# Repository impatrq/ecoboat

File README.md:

# EcoBoat
Bienvenidos al repositorio de EcoBoat.

## Software

En la carpeta de "Software" se encontrarán con varios archivos:

- EcoBoat1.0: Es el código principal, donde se ejecuta el funcionamiento del barco y todas las librerías utilizadas para dicho fin.
- Motores: Es la librería (desarrollada por el equipo de EcoBoat) que se utiliza para controlar los motores.
- SensoresUS: Es la librería (desarrollada por el equipo de EcoBoat) que utilizamos para realizar las mediciones con los sensores Ultrasónicos.
- RedNeuronal: Es la librería (desarrollada por el equipo de EcoBoat) que contiene el código de la Red Neuronal y su entrenamiento.
- Módulo_Master: Es el programa utilizado para recibir la información y transferirla mediante sockets a la Interfaz de Usuario.
- Interfaz de Usuario: En esta carpeta se encuentran los códigos de la interfaz de usuario.
- Simulación: En esta carpeta encontrarán todo lo relacionado al entrenamiento de la Red Neuronal.
  - Aplicación Ejecutable: Aquí se encuentra la aplicación de la cual se obtienen los datos de entrenamiento para la red, es decir, la red aprende de las acciones realizadas en dicha aplicación.
  - Código fuente: Contiene el programa de la simulación.
  - trainData: En esta carpeta se guardan los archivos con la información de entrenamiento.

## Hardware

En esta carpeta se encuentran los diseños de todas las placas utilizadas:

- Circuito de Control de Marcha: Circuito utilizado para controlar los 3 motores del EcoBoat
- Fuente de 12V a 5V: regulador de tensión de 12 a 5V.
- Regulador de Carga: Es el circuito que controla la carga de la batería utilizando un panel solar.
- SensoresUS: Esta placa cumple la función de sincronizar la toma de datos de los sensores Ultrasónicos.
- Diagrama de Interconexión de circuitos: Es un diagrama que muestra como se conectan todas las placas del proyecto.

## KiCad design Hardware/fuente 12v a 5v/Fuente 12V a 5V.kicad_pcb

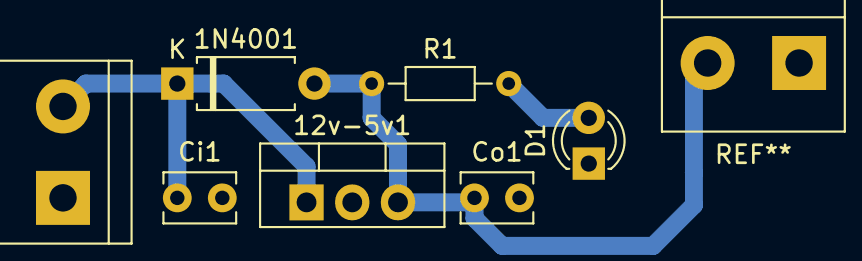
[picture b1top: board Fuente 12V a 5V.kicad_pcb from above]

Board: 2 copper layers, 7 parts (0 on the bottom side), 4 nets.

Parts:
1N4001: D; D_A-405_P7.62mm_Horizontal
12v-5v1: LM7805_TO220; TO-220-3_Vertical
Ci1: 330n; C_Disc_D3.8mm_W2.6mm_P2.50mm
Co1: 100n; C_Disc_D3.8mm_W2.6mm_P2.50mm
D1: LED; LED_D3.0mm
R1: 1K; R_Axial_DIN0204_L3.6mm_D1.6mm_P7.62mm_Horizontal
input-12v1: 12v; TerminalBlock_bornier-2_P5.08mm

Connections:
GND: 12v-5v1.2, Ci1.2, Co1.2, D1.1, input-12v1.1
unnamed: 1N4001.1, 12v-5v1.1, Ci1.1, input-12v1.2
unnamed: 1N4001.2, 12v-5v1.3, Co1.1, R1.1
unnamed: D1.2, R1.2

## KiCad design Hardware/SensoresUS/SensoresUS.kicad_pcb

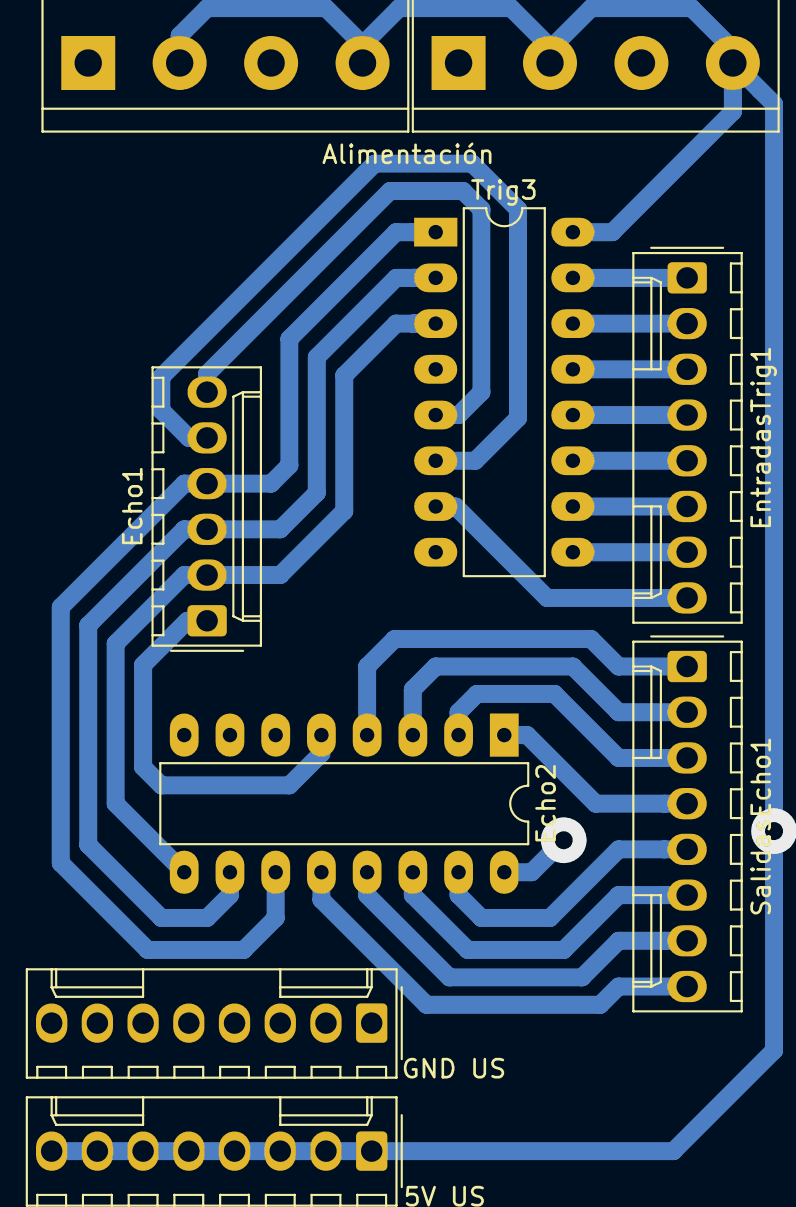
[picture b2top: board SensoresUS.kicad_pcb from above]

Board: 2 copper layers, 8 parts (0 on the bottom side), 24 nets.

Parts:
5V US: Conn_01x08_Female; Molex_KK-254_AE-6410-08A_1x08_P2.54mm_Vertical
Alimentación: DOU; TerminalBlock_bornier-4_P5.08mm
Echo1: Conn_01x01_Female; Molex_KK-254_AE-6410-06A_1x06_P2.54mm_Vertical
Echo2: 74LS151; DIP-16_W7.62mm_LongPads
EntradasTrig1: Conn_01x08_Female; Molex_KK-254_AE-6410-08A_1x08_P2.54mm_Vertical
GND US: Conn_01x08_Female; Molex_KK-254_AE-6410-08A_1x08_P2.54mm_Vertical
SalidasEcho1: Conn_01x08_Female; Molex_KK-254_AE-6410-08A_1x08_P2.54mm_Vertical
Trig3: 74HC237; DIP-16_W7.62mm_LongPads

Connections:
5V: 5V US.1, 5V US.2, 5V US.3, 5V US.4, 5V US.5, 5V US.6, 5V US.7, 5V US.8, Alimentación.2, Alimentación.4, Echo2.16, Trig3.16
GND: Alimentación.1, Alimentación.3, Echo2.7, Echo2.8, GND US.1, GND US.2, GND US.3, GND US.4, GND US.5, GND US.6, GND US.7, GND US.8, Trig3.4, Trig3.8
unnamed: Echo1.1, Echo2.5
unnamed: Echo2.1, SalidasEcho1.4
unnamed: Echo2.2, SalidasEcho1.3
unnamed: Echo2.3, SalidasEcho1.2
unnamed: Echo2.4, SalidasEcho1.1
unnamed: Echo2.12, SalidasEcho1.8
unnamed: Echo2.13, SalidasEcho1.7
unnamed: Echo2.14, SalidasEcho1.6
unnamed: Echo2.15, SalidasEcho1.5
unnamed: EntradasTrig1.1, Trig3.15
unnamed: EntradasTrig1.2, Trig3.14
unnamed: EntradasTrig1.3, Trig3.13
unnamed: EntradasTrig1.4, Trig3.12
unnamed: EntradasTrig1.5, Trig3.11
unnamed: EntradasTrig1.6, Trig3.10
unnamed: EntradasTrig1.7, Trig3.9
unnamed: EntradasTrig1.8, Trig3.7
unnamed: Echo1.5, Trig3.6
unnamed: Echo1.6, Trig3.5
Select1: Echo1.4, Echo2.11, Trig3.1
Select2: Echo1.3, Echo2.10, Trig3.2
Select3: Echo1.2, Echo2.9, Trig3.3

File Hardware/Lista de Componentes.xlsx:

Componente |  | Cantidad
Placa de Cobre 20x15 |  | 1
Cloruro Férrico |  | 1
Molex Macho 2 Pines |  | 2
Molex Hemra 2 Pines |  | 2
Molex Macho 3 Pines |  | 1
Molex Hembra 3 Pines |  | 1
Molex Macho 4 Pines |  | 2
Molex Hembra 4 Pines |  | 2
Molex Macho 6 Pines |  | 1
Molex Hembra 6 Pines |  | 1
Molex Macho 7 Pines |  | 1
Molex Hembra 7 Pines |  | 1
Molex Macho 8 Pines |  | 4
Molex Hembra 8 Pines |  | 4
Conectores para Molex |  | 80 | (Terminales utilizados para conectar un cable a un molex hembra)
Pines Hembra a Macho |  | 40
Termocontraible |  | 80cm
Bornera 2 Pines |  | 8
Bornera 5 Pines |  | 1
Bornera 4 Pines |  | 2
MOSFET IRF9530 |  | 5
MOSFET IRF640 |  | 5
Transistores BJT |  | 8
Resistencia 220 |  | 8
Resistencia 1K |  | 1
Resistencia 1,2K |  | 1
Resistencia 10K |  | 8
Resistencia 82K |  | 1
Resistencia 270K |  | 1
Preset 200K |  | 1
Preset 500K |  | 1
Diodo |  | 1
Diodo Zener 15V |  | 1
Diodo LED |  | 2
Fusible 10A |  | 1
Capacitor 330nF |  | 3
Capacitor 100nF |  | 3
LM7805 |  | 2
Operacional |  | 1
UNL2003 |  | 1
MCP3008 |  | 1
74HC237 |  | 1
74LS151 |  | 1
ACS712 ±20A |  | 2
Módulo RF NRF24 |  | 2
Batería ciclo profundo |  | 1
Panel Solar |  | 1

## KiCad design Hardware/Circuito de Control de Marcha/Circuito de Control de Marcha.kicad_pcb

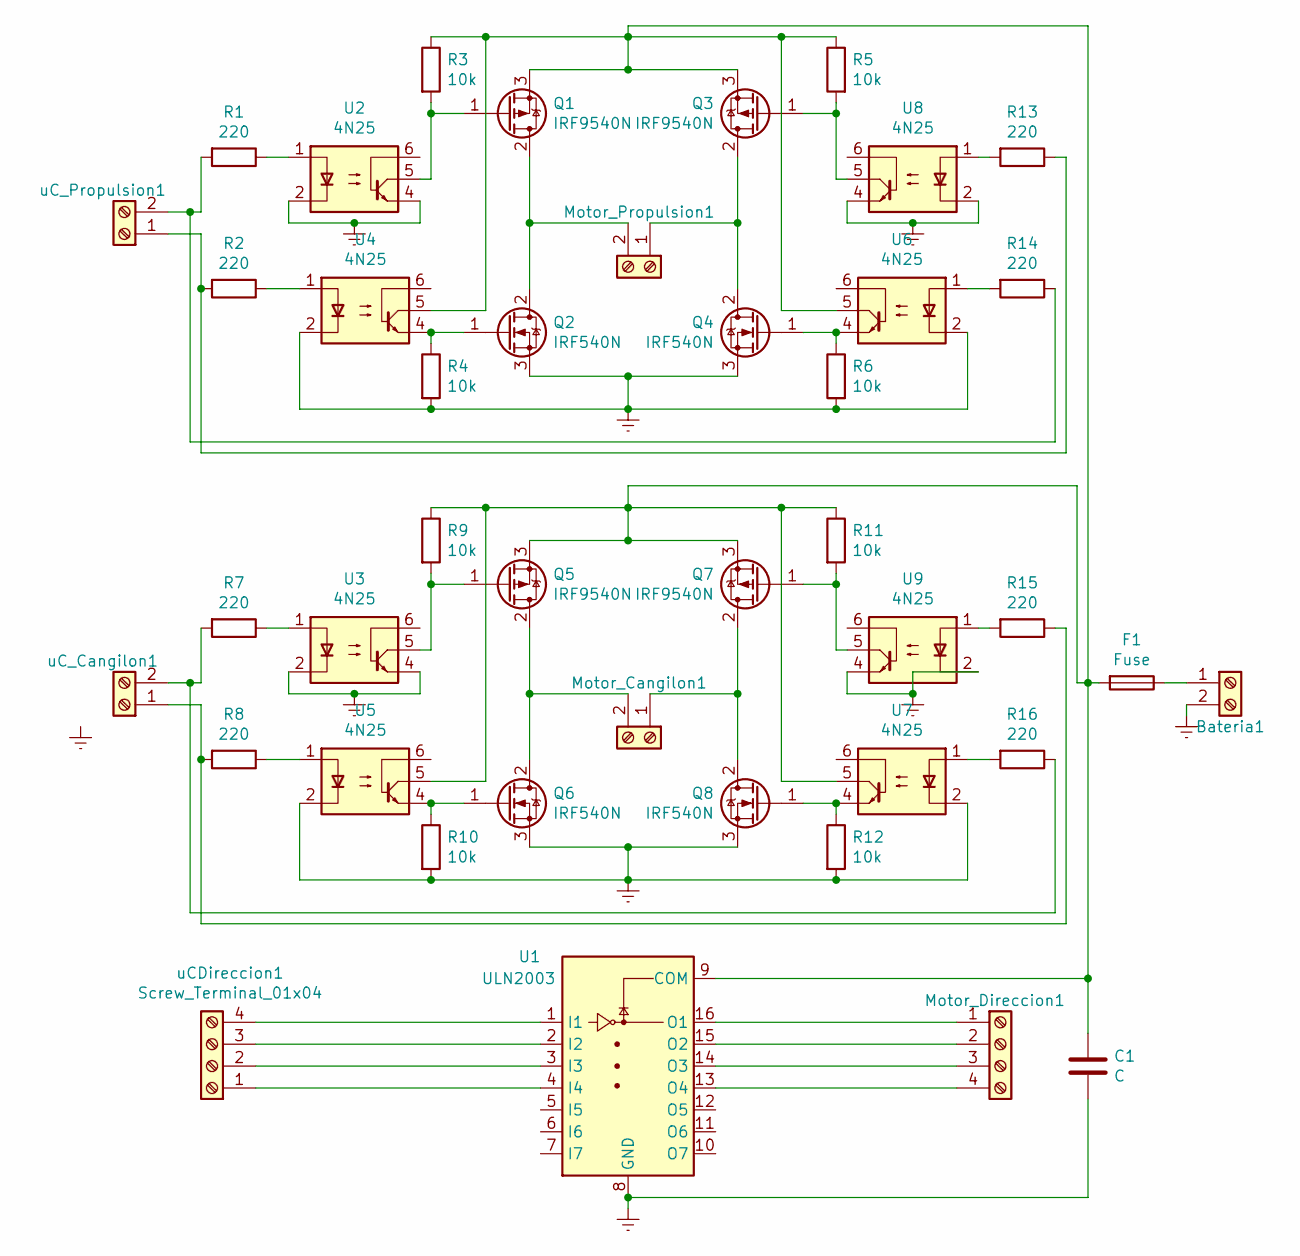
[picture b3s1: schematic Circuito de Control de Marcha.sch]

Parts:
Bateria1: Screw_Terminal_01x02; TerminalBlock_bornier-2_P5.08mm
C1: C; C_Disc_D4.3mm_W1.9mm_P5.00mm
F1: Fuse; Fuse_Blade_Mini_directSolder
Motor_Cangilon1: Screw_Terminal_01x02; TerminalBlock_bornier-2_P5.08mm
Motor_Direccion1: Screw_Terminal_01x04; Molex_KK-254_AE-6410-04A_1x04_P2.54mm_Vertical
Motor_Propulsion1: Screw_Terminal_01x02; TerminalBlock_bornier-2_P5.08mm
Q1, Q3, Q5, Q7: IRF9540N; TO-220-3_Vertical
Q2, Q4, Q6, Q8: IRF540N; TO-220-3_Vertical
R1, R2, R7, R8, R13, R14, R15, R16: 220; R_Axial_DIN0204_L3.6mm_D1.6mm_P7.62mm_Horizontal
R3, R4, R5, R6, R9, R10, R11, R12: 10k; R_Axial_DIN0204_L3.6mm_D1.6mm_P7.62mm_Horizontal
U1: ULN2003; DIP-14_W10.16mm
U2, U3, U4, U5, U6, U7, U8, U9: 4N25; DIP-6_W7.62mm
uCDireccion1: Screw_Terminal_01x04; Molex_KK-254_AE-6410-04A_1x04_P2.54mm_Vertical
uC_Cangilon1: Screw_Terminal_01x02; Molex_KK-254_AE-6410-02A_1x02_P2.54mm_Vertical
uC_Propulsion1: Screw_Terminal_01x02; Molex_KK-254_AE-6410-02A_1x02_P2.54mm_Vertical

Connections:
Earth: Bateria1.2, C1.2, Q2.3 (S), Q4.3 (S), Q6.3 (S), Q8.3 (S), R4.2, R6.2, R10.2, R12.2, U1.8 (GND), U2.2, U2.4, U3.2, U3.4, U4.2, U5.2, U6.2, U7.2, U8.2, U8.4, U9.2, U9.4; also elsewhere on the board
unnamed: Bateria1.1, F1.1
unnamed 2: C1.1, F1.2, Q1.3 (S), Q3.3 (S), Q5.3 (S), Q7.3 (S), R3.1, R5.1, R9.1, R11.1, U1.9 (COM), U4.5, U5.5, U6.5, U7.5; also elsewhere on the board
unnamed: Motor_Cangilon1.1, Q7.2 (D), Q8.2 (D)
unnamed: Motor_Cangilon1.2, Q5.2 (D), Q6.2 (D)
unnamed 5: Motor_Direccion1.1, U1.16 (O1); also elsewhere on the board
unnamed 6: Motor_Direccion1.2, U1.15 (O2); also elsewhere on the board
unnamed 7: Motor_Direccion1.3, U1.14 (O3); also elsewhere on the board
unnamed 8: Motor_Direccion1.4, U1.13 (O4); also elsewhere on the board
unnamed: Motor_Propulsion1.1, Q3.2 (D), Q4.2 (D)
unnamed: Motor_Propulsion1.2, Q1.2 (D), Q2.2 (D)
unnamed: Q1.1 (G), R3.2, U2.5
unnamed: Q2.1 (G), R4.1, U4.4
unnamed: Q3.1 (G), R5.2, U8.5
unnamed: Q4.1 (G), R6.1, U6.4
unnamed: Q5.1 (G), R9.2, U3.5
unnamed: Q6.1 (G), R10.1, U5.4
unnamed: Q7.1 (G), R11.2, U9.5
unnamed: Q8.1 (G), R12.1, U7.4
unnamed: R1.1, U2.1
unnamed: R1.2, R14.1, uC_Propulsion1.2
unnamed: R2.1, U4.1
unnamed: R7.1, U3.1
unnamed: R8.1, U5.1
unnamed: R2.2, R13.1, uC_Propulsion1.1
unnamed: R13.2, U8.1
unnamed: R14.2, U6.1
unnamed: R8.2, R15.1, uC_Cangilon1.1
unnamed: R15.2, U9.1
unnamed: R7.2, R16.1, uC_Cangilon1.2
unnamed: R16.2, U7.1
unnamed 31: U1.1 (I1), uCDireccion1.4; also elsewhere on the board
unnamed 32: U1.2 (I2), uCDireccion1.3; also elsewhere on the board
unnamed 33: U1.3 (I3), uCDireccion1.2; also elsewhere on the board
unnamed 34: U1.4 (I4), uCDireccion1.1; also elsewhere on the board

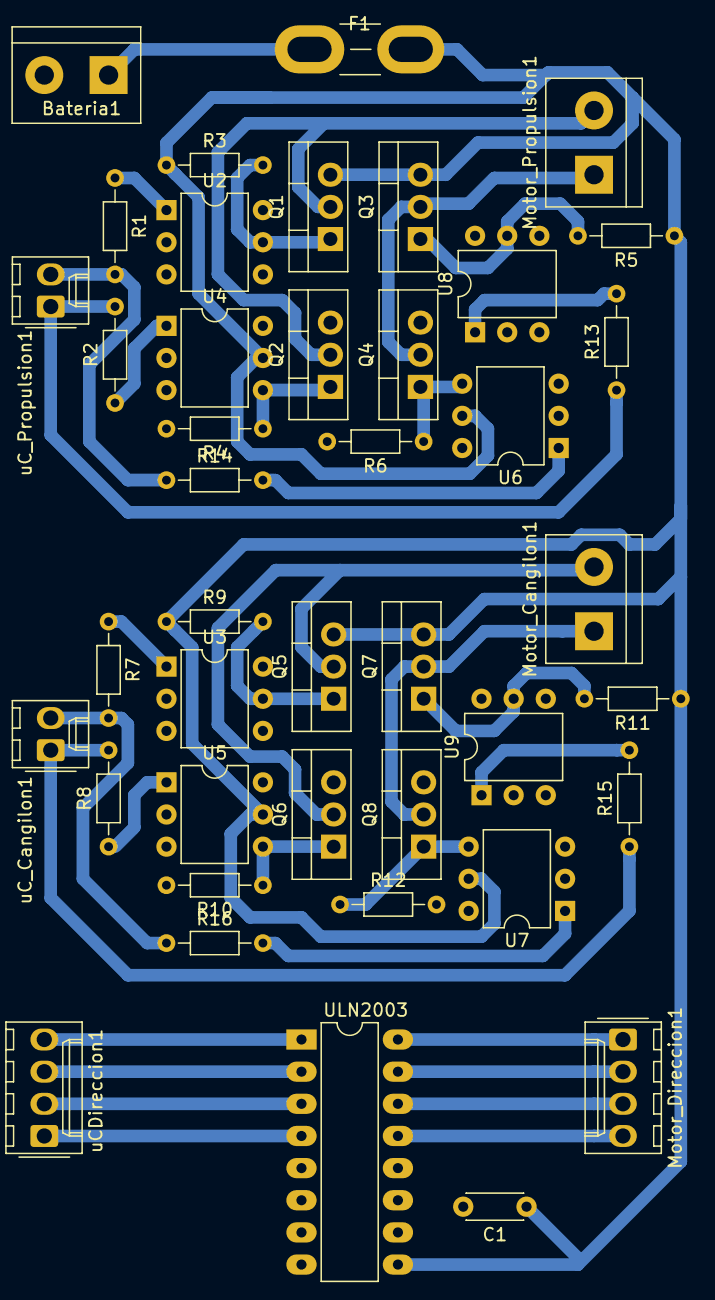
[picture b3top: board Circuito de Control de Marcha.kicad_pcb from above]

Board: 2 copper layers, 42 parts (0 on the bottom side), 35 nets.

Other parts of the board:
ULN2003: ULN2003; DIP-16_W7.62mm_LongPads

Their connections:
Earth: ULN2003.8; also elsewhere on the board
unnamed 2: ULN2003.9; also elsewhere on the board
unnamed 5: ULN2003.16; also elsewhere on the board
unnamed 6: ULN2003.15; also elsewhere on the board
unnamed 7: ULN2003.14; also elsewhere on the board
unnamed 8: ULN2003.13; also elsewhere on the board
unnamed 31: ULN2003.1; also elsewhere on the board
unnamed 32: ULN2003.2; also elsewhere on the board
unnamed 33: ULN2003.3; also elsewhere on the board
unnamed 34: ULN2003.4; also elsewhere on the board

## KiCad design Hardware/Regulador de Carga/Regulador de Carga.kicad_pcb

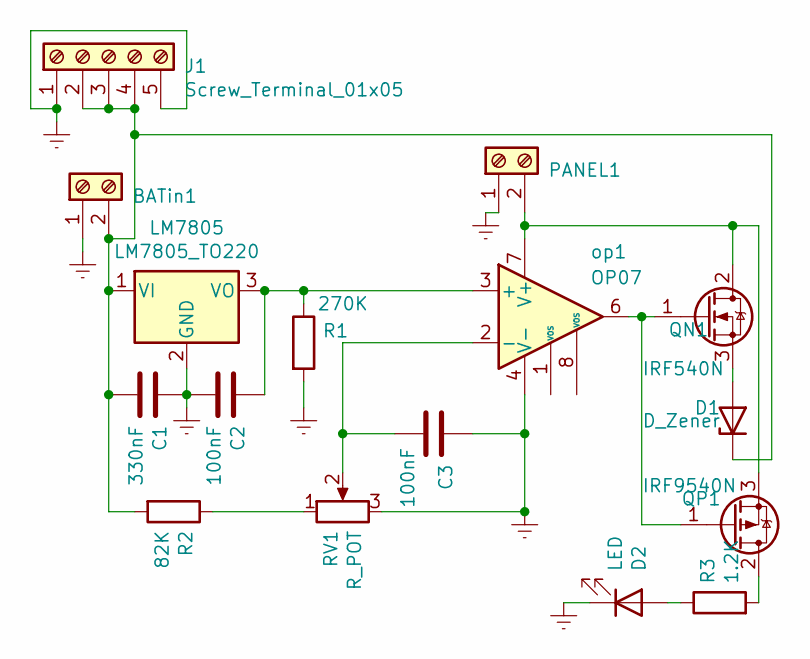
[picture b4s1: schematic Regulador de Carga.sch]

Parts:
BATin1: Screw_Terminal_01x02; TerminalBlock_bornier-2_P5.08mm
C1: 330nF; C_Disc_D4.3mm_W1.9mm_P5.00mm
C2, C3: 100nF; C_Disc_D4.3mm_W1.9mm_P5.00mm
D1: D_Zener; D_DO-15_P12.70mm_Horizontal
D2: LED; LED_D3.0mm
J1: Screw_Terminal_01x05; TerminalBlock_bornier-5_P5.08mm
LM7805: LM7805_TO220; TO-220-3_Vertical
PANEL1: Screw_Terminal_01x02; TerminalBlock_bornier-2_P5.08mm
QN1: IRF540N; TO-220-3_Vertical
QP1: IRF9540N; TO-220-3_Vertical
R1: 270K; R_Axial_DIN0204_L3.6mm_D1.6mm_P7.62mm_Horizontal
R2: 82K; R_Axial_DIN0204_L3.6mm_D1.6mm_P7.62mm_Horizontal
R3: 1.2K; R_Axial_DIN0204_L3.6mm_D1.6mm_P7.62mm_Horizontal
RV1: R_POT; Potentiometer_ACP_CA14-H5_Horizontal
op1: OP07; DIP-8_W7.62mm

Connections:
Earth: BATin1.1, C1.1, C2.2, C3.1, D2.1 (K), J1.1, J1.5, LM7805.2 (GND), PANEL1.1, R1.2, RV1.3, op1.4 (V-)
unnamed: BATin1.2, C1.2, D1.1 (K), J1.2, J1.3, J1.4, LM7805.1 (VI), R2.2
unnamed: C2.1, LM7805.3 (VO), R1.1, op1.3 (+)
unnamed: C3.2, RV1.2, op1.2 (-)
unnamed: D1.2 (A), QN1.3 (S)
unnamed: D2.2 (A), R3.1
unnamed: PANEL1.2, QN1.2 (D), QP1.3 (S), op1.7 (V+)
unnamed: QN1.1 (G), QP1.1 (G), op1.6
unnamed: QP1.2 (D), R3.2
unnamed: R2.1, RV1.1

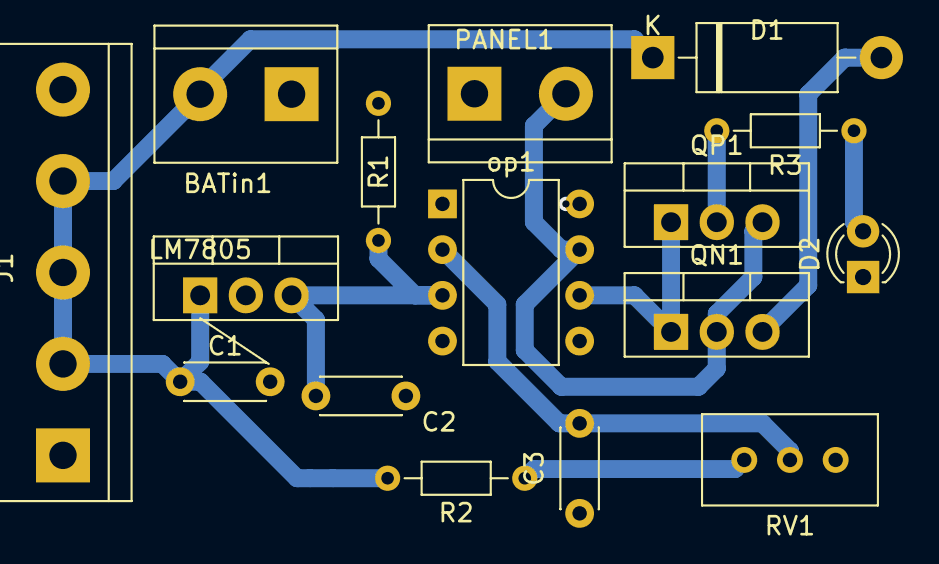
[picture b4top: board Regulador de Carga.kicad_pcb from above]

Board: 2 copper layers, 16 parts (0 on the bottom side), 10 nets.

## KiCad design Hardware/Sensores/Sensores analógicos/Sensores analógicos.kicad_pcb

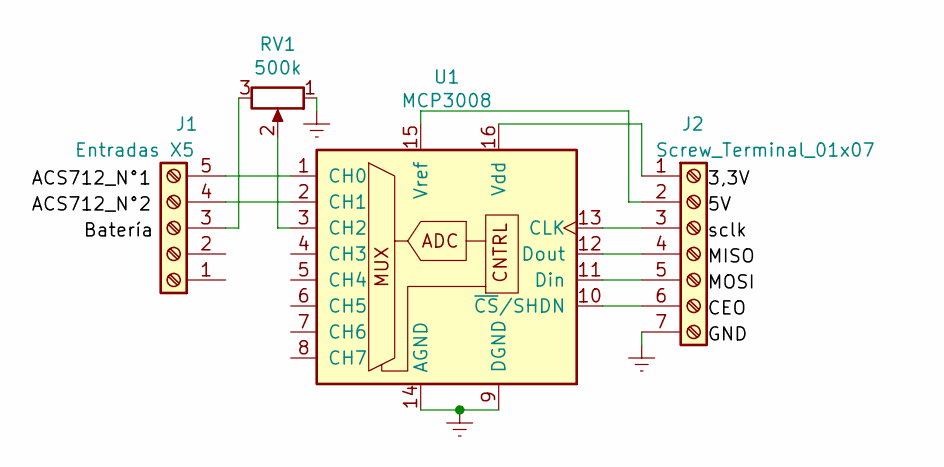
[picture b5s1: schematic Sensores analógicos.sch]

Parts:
J1: Entradas X5; Molex_KK-254_AE-6410-05A_1x05_P2.54mm_Vertical
J2: Screw_Terminal_01x07; Molex_KK-254_AE-6410-07A_1x07_P2.54mm_Vertical
RV1: 500k; Potentiometer_Bourns_3006P_Horizontal
U1: MCP3008; DIP-16_W7.62mm

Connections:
Earth: J2.7, RV1.1, U1.9 (DGND), U1.14 (AGND)
unnamed: J1.3, RV1.3
unnamed: J1.4, U1.2 (CH1)
unnamed: J1.5, U1.1 (CH0)
unnamed: J2.1, U1.16 (Vdd)
unnamed: J2.2, U1.15 (Vref)
unnamed: J2.3, U1.13 (CLK)
unnamed: J2.4, U1.12 (Dout)
unnamed: J2.5, U1.11 (Din)
unnamed: J2.6, U1.10 (~CS~/SHDN)
unnamed: RV1.2, U1.3 (CH2)

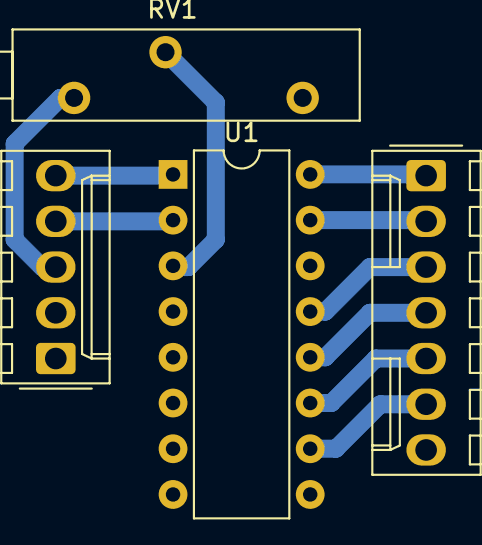
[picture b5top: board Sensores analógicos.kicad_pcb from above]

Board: 2 copper layers, 4 parts (0 on the bottom side), 11 nets.

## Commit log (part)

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2020-05-06 definimos las funciones basicas
2020-05-06 se agregaron los parametros de las funciones y se las invoco
2020-05-06 Update main.py
    Correxión de parentesis en el print y faltaba agregar el resulatado en la funcion de muestraDeResultado
2020-05-06 Update main.py
    Se creo la funcion de tomaDeValores
2020-05-07 Create Introduccion.docx
    Escribimos la introduccion
2020-05-11 Delete main.py
    Borro el trabajo que hicimos de prueba con medina
2020-05-11 Archivo de proteus
    Cree un archivo de proteus para los modulos de RF
2020-05-11 Estructura receptor RF
    Se creo la estructura del receptor de RF en proteus
2020-05-11 Borre los archivos de proteus
    No nos servia de nada probarlo en proteus porque no se pueden simular 2 raspberrys
2020-05-11 Create Módulo Transmisor.py
    Cree la estructura del modulo transmisor, solo faltaria tomar los datos necesarios para enviar
2020-05-12 Revert "Cree carpetas"
    This reverts commit 64196b51676b2694d90ba39ffbe1830383c1fe42.
2020-05-12 Carpeta de Software
2020-05-12 Carpeta de Diseño
2020-05-12 Carpeta de Documentacion
2020-05-12 Cambiar el icono de la carpeta hardware
2020-05-14 Simular regulador de carga
2020-05-14 Agregar huellas faltantes
    le agregue las huellas que faltaban al regulador de carga
2020-05-15 motores
    libreria para controlar los motores
    falta imrementacion de pwm
2020-05-15 Update instrucciones libreria motores.txt
    no le den bola a esto
2020-05-16 Update EstructuraPilotoAutomatico.py
    cambie un par de cositas que habia escrito mal
2020-05-17 Historia sobre el dia internacional del reciclaje
2020-05-17 Create After Effects.ai
    Crear un archivo para que amrcos puedas hacer el video
2020-05-18 Update After Effects capa.ai
    separando mas capas, las capas separadas antes no eran suficientes
2020-05-18 Update After Effects capa.ai
    agregar mas capas
2020-05-18 Delete After Effects capa.ai
    borar por q no me sirve
2020-05-19 Update EstructuraPilotoAutomatico.py
    Agregar funcion que evite choques
2020-05-19 Subir archivos de blender
2020-05-19 Animacion blender
    Cree la animacion de blender hay que achicar todo y cambiar los colores para poder renderzarlo
2020-05-19 gps
    libreria para el control del gps
2020-05-20 Animacion
    Primera animacion completa, faltan realizar algunos cambios menores
2020-05-20 Crear imagen de integrantes
2020-05-21 Borrar todos los modelos 3D al pedo
2020-05-21 gps
    agregue la funcio de calculo de rumbo deseado
2020-05-22 modulos RF
    emprolije un poco el codigo para usarlo mas facil
2020-05-22 Create inicio de presentacion.mov
    video de presentacion
2020-05-22 Create presentacion.rar
    rar de la presentacion
2020-05-22 Delete Logo.ai
    molestaba para pasar
2020-05-22 Delete After Effects.ai
    molestaba para pasar
2020-05-26 Update Fondo.ai
    mas capas
2020-05-26 Receptor
    me olvide de guardar estos cambios
2020-05-26 Create Animación.mp4
    Agregar la animación con fondo para insta.
2020-05-26 Create Animación Logo.mp4
    Convertir la animación del logo a mp4.
2020-05-27 Update Módulo Slave.py
    Agregue una writing pipe que me habia olvidado
2020-05-27 transeptores
    cambios en las funciones del slave
2020-05-27 actualizacion pagina
2020-05-27 Simular el regulador de carga
    Lo simule usando 4 diodos en directa. Funciona bien.
2020-05-27 Esquematico Regulador de Carga
    Agregue los 4 diodos en el esquematico.
2020-05-27 piloto automatico
    cambio en los datos de entrada de las funciones
2020-05-27 Update Módulo Slave.py
    Agregue los datos del gps al modulo esclavo.
2020-05-27 modulos RF
    cambios en master y slave
2020-05-28 Update Módulo Slave.py
    Le asigne pines de entrada a los datos que tiene que tomar del barco. Tambien termine de declarar todas las variables que se van a enviar.
2020-05-28 Create Pines utilizados (Raspberry del barco).txt
    Hice una lista de los pines que estan usados.
2020-05-28 Le saque el fondo a las partes
2020-06-01 Cambios al diseño de la interfaz de usuario
2020-06-01 Guardar objetos como PNG
2020-06-01 Adaptar el fondo para la página
2020-06-01 Cambiar el color del fondo
2020-06-02 Eliminar archivos que estan de mas
2020-06-03 asdf
2020-06-03 Create eklos.docx
    para la pagina eklos
2020-06-04 Historia dia munidal del medio ambiente
    Hice una historia para subir a insta por el día mundial del medio ambiente.
2020-06-05 Create Historia página actualizada.ai
    Hacer el diseño de la historia
2020-06-07 Hacer historia sobre que actualizamos la pagina
2020-06-07 Actualice el PCB del regulador de carga
2020-06-07 Gaurdar las fotos del RC
2020-06-07 Corregir errores del RC
2020-06-08 Historia sobre el dia mundial de los oceanos
2020-06-08 Placa SUS
    Cambio de integrados
2020-06-11 Simular el regulador de carga
2020-06-11 Actualizar el esquemático
2020-06-11 Detalles del PCB
2020-06-11 Sacar captura para trello
2020-06-12 Threading
    uni los progamas del PA, modulos RF y GPS para utilizar Threading a traves de u unico codigo
2020-06-17 sensoresUS
    estructure la libreria
2020-06-17 Programa de Qt
    Programa final de Qt con las librerias de Wiring Pi, Píxmap y la libreria gps de Qt
2020-06-18 Pruebas
    Hice pruebas mas parecidas a lo que vamos a hacer nosotros
2020-06-23 Conexion Remota
    Use remote para conectarme desde dos redes diferentes.
2020-06-24 Actualizacion Piloto Automatico
    Agregue el modulo slave a la programacion del piloto automatico e hice un par de cambios chiquitos a la programacion general.
2020-06-25 PCB de los sensores de corriente
2020-06-25 Update EstructuraPilotoAutomatico.py
    Agregue la programacion de los sensores de corriente.
2020-06-27 Esquematico sensor porcentaje de bateria
2020-06-27 Update EstructuraPilotoAutomatico.py
    Agregue la programacion del sensor de porcentaje de bateria
2020-06-29 DIagrama de interconexion de circuitos
    Hice un diagrama con todas las conexiones que vamos a tener que hacer en el barco
2020-06-29 Actualizacion de placas
2020-06-29 Correxion en el control de marcha
2020-07-01 Create Primeras pruebas Módulo Slave.py
    Hice un programa de el modulo de RF slave para hacer las primeras pruebas.
2020-07-01 Create Primeras_pruebas_M_dulo_Master.ino
    Programe el modulo master en arduino
2020-07-02 Preparar para impresion
    Prepare todas las placas para imprimirlas
2020-07-02 Update EstructuraPilotoAutomatico.py
    terminada la parte del gps
2020-07-02 prueba de gps y PA
    codigo para probar el piloto automatico y el gps
2020-07-02 prueba de motores
    programa para probar los puente H y el paso a paso
2020-07-02 Update pruebaMOT.py
    faltaba la configuracion del GPIO
2020-07-04 Pruebas con optoacopladores
    Hice pruebas con optoacopladores para el circuito de control de marcha
2020-07-04 PCB control de marcha
    Intente hacer el PCB pero me queda una conexion de los púentes H
2020-07-04 Circuito de Control de Marcha
    Correccion de PCB
2020-07-06 Update and rename deteccion-py.py to deteccion.py
    le arregle el nombre
2020-07-07 Agregar USB y errores de impresion
    Agregue un conector USB al regulador de 5V y corregí los errores de impresión
2020-07-07 CCM
    agregue un mux en el puente del cangilon para controlarlo con un solo pwm
2020-07-07 lista de componentes
2020-07-07 PilotoA
    cambio de variables en el PA para tener el codigo mas prolijo
2020-07-08 Diagrama de interconexion de circuitos
    Cambie los pines de la raspberry para que coincidan con los cambios que hicimos por el PWM y lo emprolijé un poco.
2020-07-13 piloto automatico
    cambio en la formula de giro
2020-07-14 PA
    saque un sleep que estaba de mas
2020-07-14 Update deteccion.py
    Primer orientacion al programa de evitar obstaculos
2020-07-14 Evitar obstaculos
    Hice el programa que vamos a usar para evitar obstaculos. Esta seria la primer version con los ocho sensores.
2020-07-17 Cambios programacion
    Hice algunos retoques en la programacion de algunas cosas que estaban mal o no estaban comentadas
2020-07-23 Conversor analogico digital
    cambie la programacion para usar el nuevo chip ADC
2020-07-24 Revisar el codigo de los modulos RF
    Cambie un par de cosas que estaban mal en el codigo de los modulos
2020-07-24 PID
    chequeo de codigo PID
2020-07-25 Update PID.py
    Agregue un comentario
2020-07-26 Update Carpeta Técnica EcoBoat.docx
    iNTRODUCCION
2020-08-06 Pasarle el fondo de instagram a yeti
2020-08-07 Update fp-info-cache
2020-08-10 RN
    codigo de entrenamiento de red neuronal listo
2020-08-10 RN
    Faltaba el ajuste de los bias
2020-08-10 Update RedNeuronal.py
    filtros para las entradas y salidas de la RN
2020-08-11 Update Primeras_pruebas_M_dulo_Master.ino
    Compile el programa y cambie errores de sintaxis
2020-08-12 Update Primeras_pruebas_M_dulo_Master.ino
    Agregué unos prints para saber cuando se está mandando el mensaje y que opción se eligió.
2020-08-19 Create EcoBoat1.0.py
    Hice un programa para lo que sería la primer versión del barco
2020-08-19 Programa para probar motores
2020-08-19 red neuronal
    cambio en las funciones activadoras
2020-08-24 CorreccionGPIO
    mismo problema que en los motores
2020-08-25 Aplicacion terminada
    Aca subo la aplicacion, perdon por no subirla antes, me habia olvidado.
2020-09-05 sensores US
    cambios en el codigo
2020-09-06 Avances en la carpeta tecnica
2020-09-08 Actualización de la carpeta tecnica
2020-09-10 Avances en la carpeta tecnica
    LLegue hasta el CCM
2020-09-13 Segui con la carpeta tecnica
    Llegue hasta el mux del CCM
2020-09-13 Actualizar carpeta técnica
2020-09-14 Carpeta tecnica GPS
    Descripcion de siftware utilizado para el GPS
2020-09-14 Probar medir distancia con el GPS
2020-09-16 Codigo GPS
    Cambio en la lectura de datos
2020-09-16 CT GPS
    teminada el apartado de GPS en la carpeta tecnica
2020-09-19 Update Diagrama de interconexión de circuitos.ai
    Agregue algunas cosas que faltaban
2020-09-20 Update EcoBoat1.0.py
    Emprolije el codigo para poder publicarlo. Faltan agrega un par de cosas
2020-09-21 Completando codigos
2020-09-21 Simulacion
    codigo terminado de la simulacion para entrenar la red neuronal
2020-09-22 simulacion
    arreglo de dos bugs
2020-09-23 Jugar con la simulación
2020-09-23 simulacion
    agregue el delta a los datos de curso y curso deseado
2020-09-23 Juegar con simulacion
2020-09-23 Revert "Juegar con simulacion"
    This reverts commit 7f76536615141b28521b4e4c5f1dff92085f24e4.
2020-09-24 Cambios en la carpeta tecnica
2020-09-24 red neuronal
2020-09-25 Anexo
    Fuentes:
    https://www.iagua.es/respuestas/que-es-contaminacion-agua
    https://www.lenntech.es/faq-contaminacion-agua.htm#:~:text=La%20contaminaci%C3%B3n%20del%20agua%20es,a%20menudo%20problemas%20de%20salud.
    https://www.nationalgeographic.es/medio-ambiente/2017/10/del-oceano-al-grifo-la-contaminacion-del-agua-nos-afecta-todos
    https://www.who.int/es/news-room/fact-sheets/detail/drinking-water
    https://www.fundacionaquae.org/agua-y-contaminacion/
2020-09-25 Update Carpeta Técnica EcoBoat.docx
    Termine con la Electronica y puse hipervinculos
2020-09-26 red neuronal
    prueba de entrenamiento, otra vez sin resultados
2020-09-27 red neuronal
    de a poco voy descubriendo como mejorarla, sigo sin resultados
2020-10-02 carpeta tecnica
    Red neuronal
    sensores ultrasonicos
2020-10-05 Prueba de sliders
2020-10-05 no se que es esto
    .
2020-10-05 Cambios chicos y comentarios
    Acomode todos los codigos y los termine de comentar para que queden mas prolijos y entendibles
2020-10-06 carpeta tecnica
    Termine la parte de pid
2020-10-07 Retoques a la carpeta tecninca
    Arregle las tabulaciones de la parte de software y complete el inicio
2020-10-08 Update Carpeta Técnica EcoBoat.docx
    Diagrama de sensores ultrasonicos
2020-10-08 Carpeta tecnica
    Agregue un esquema de la red neuronal
2020-10-14 Logo png
2020-10-14 Carpeta tecnica terminada
2020-10-14 Cambios del Comodoro en la carpeta tecnica
2020-10-16 Acomodar la parte de IU
